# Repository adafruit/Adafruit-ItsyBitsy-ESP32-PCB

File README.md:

## Adafruit ItsyBitsy ESP32 8 MB Flash / 2 MB PSRAM PCB

<a href="http://www.adafruit.com/products/5889"><br/>
Click here to purchase one from the Adafruit shop</a>

PCB files for the Adafruit ItsyBitsy ESP32 8 MB Flash / 2 MB PSRAM: wFL Antenna and PCB Antenna. 

Format is EagleCAD schematic and board layout
* https://www.adafruit.com/product/5889
* https://www.adafruit.com/product/5890

### Description

What's smaller than a Feather but larger than a Trinket? It's an Adafruit ItsyBitsy ESP32, a powerful processor PCB with a plethora of pins! It features the ESP32 Pico module, an FCC-certified module that contains an ESP32 chip with dual-core 240MHz Tensilica processor, WiFi, and Bluetooth classic + BLE, configured with 8 MB of Flash memory, and 2 MB of PSRAM.

We've added some handy accessories like a USB to serial converter chip, power regulator, USB Micro B, buttons, NeoPixel, and Stemma QT I2C connector to outfit this super-hero chip for any task you want to throw it at. This is also an ultra low power ESP32 board with a deep sleep current consumption of 10uA!

At the core of the Itsy is the ESP32 (PICO ECO V3) chip, which is a single 2.4 GHz Wi-Fi and Bluetooth combo chip designed with TSMC’s 40 nm low-power technology. The ESP32 PICO in particular integrates all peripheral components seamlessly, including a crystal oscillator, flash, PSRAM, filter capacitors, and RF matching links in one single package. This makes it perfect for stuffing into a small space as the ItsyBitsy.

Please note, like other ESP32 modules, the ItsyBitsy ESP32 does not have native USB support - instead, there's a USB to serial converter chip. This means it cannot act like a USB keyboard or mouse, but it does have BLE and BT classic, so you could use it wirelessly.

Here are some of the updates you can look forward to when using ItsyBitsy ESP32:

* Same size, form-factor as the remaining ItsyBitsy mainboards - with a similar but not identical pinout (there are no pins at the end of the board like most other Itsy's due to the radio antenna being there)
* USB Micro B - To maintain compatibility with the rest of the ItsyBitsy's
* ESP32 V2 03 Dual Core 240MHz Xtensa processor - the ESP32 you know and love, with the latest engineering fixes. Massive user base and thousands of existing projects and libraries to use.
* WiFi, Bluetooth LE, and BT Classic for any IoT project usage
* 8 MB Flash & 2 MB PSRAM
* USB to Serial converter built-in with high-speed UART for debugging and uploading, auto-reset circuit works perfectly with any ESP32 uploading tool.
* Can be used with Arduino IDE, CircuitPython or MicroPython
* Built-in RGB NeoPixel LED with power control to reduce quiescent power in deep sleep
* Built-in Red LED on pin D13
* 5V level-shifted output on D5, perfect for driving NeoPixels or other devices that want 5V logic signal
* Battery input pads on the underside with diode protection for external battery packs up to 6V input
* 20 General Purpose "IO" pins:
	* 20 Pads expose pins from the ESP32:
	* 3 are analog input only (A3, A4, A5)
	* 1 is digital output only (5) with 5V level shifted up
	* 13 x 12-bit analog inputs (A0, A1, A2, A3, A4, A5, D12, D13, D14, SDA, SCL, D32, D33)
	* Dual 8-bit analog output DACs on A0/A1
	* PWM outputs on any pin
	* I2C port with STEMMA QT plug-n-play connector - a second I2C port can be defined on any other pins.
	* Hardware UART in addition to the USB-serial UART
	* Hardware SPI on the high speed SPI peripheral pins - a second SPI port can be defined on any other pins.
	* Hardware I2S on any pins
	* 8 x Capacitive Touch with no additional components required
* 3.3V regulator with 600mA peak output
* Light sleep at 4mA, deep sleep at ~10uA
* Reset switch for starting your project code over, for entering bootloader mode or for user reading
* User switch on pin 35
* Really small

Each order comes with one assembled and tested ItsyBitsy ESP32 with headers that can be soldered in for use with a breadboard.

### License

Adafruit invests time and resources providing this open source design, please support Adafruit and open-source hardware by purchasing products from [Adafruit](https://www.adafruit.com)!

Designed by Limor Fried/Ladyada for Adafruit Industries.

Creative Commons Attribution/Share-Alike, all text above must be included in any redistribution. 
See license.txt for additional details.

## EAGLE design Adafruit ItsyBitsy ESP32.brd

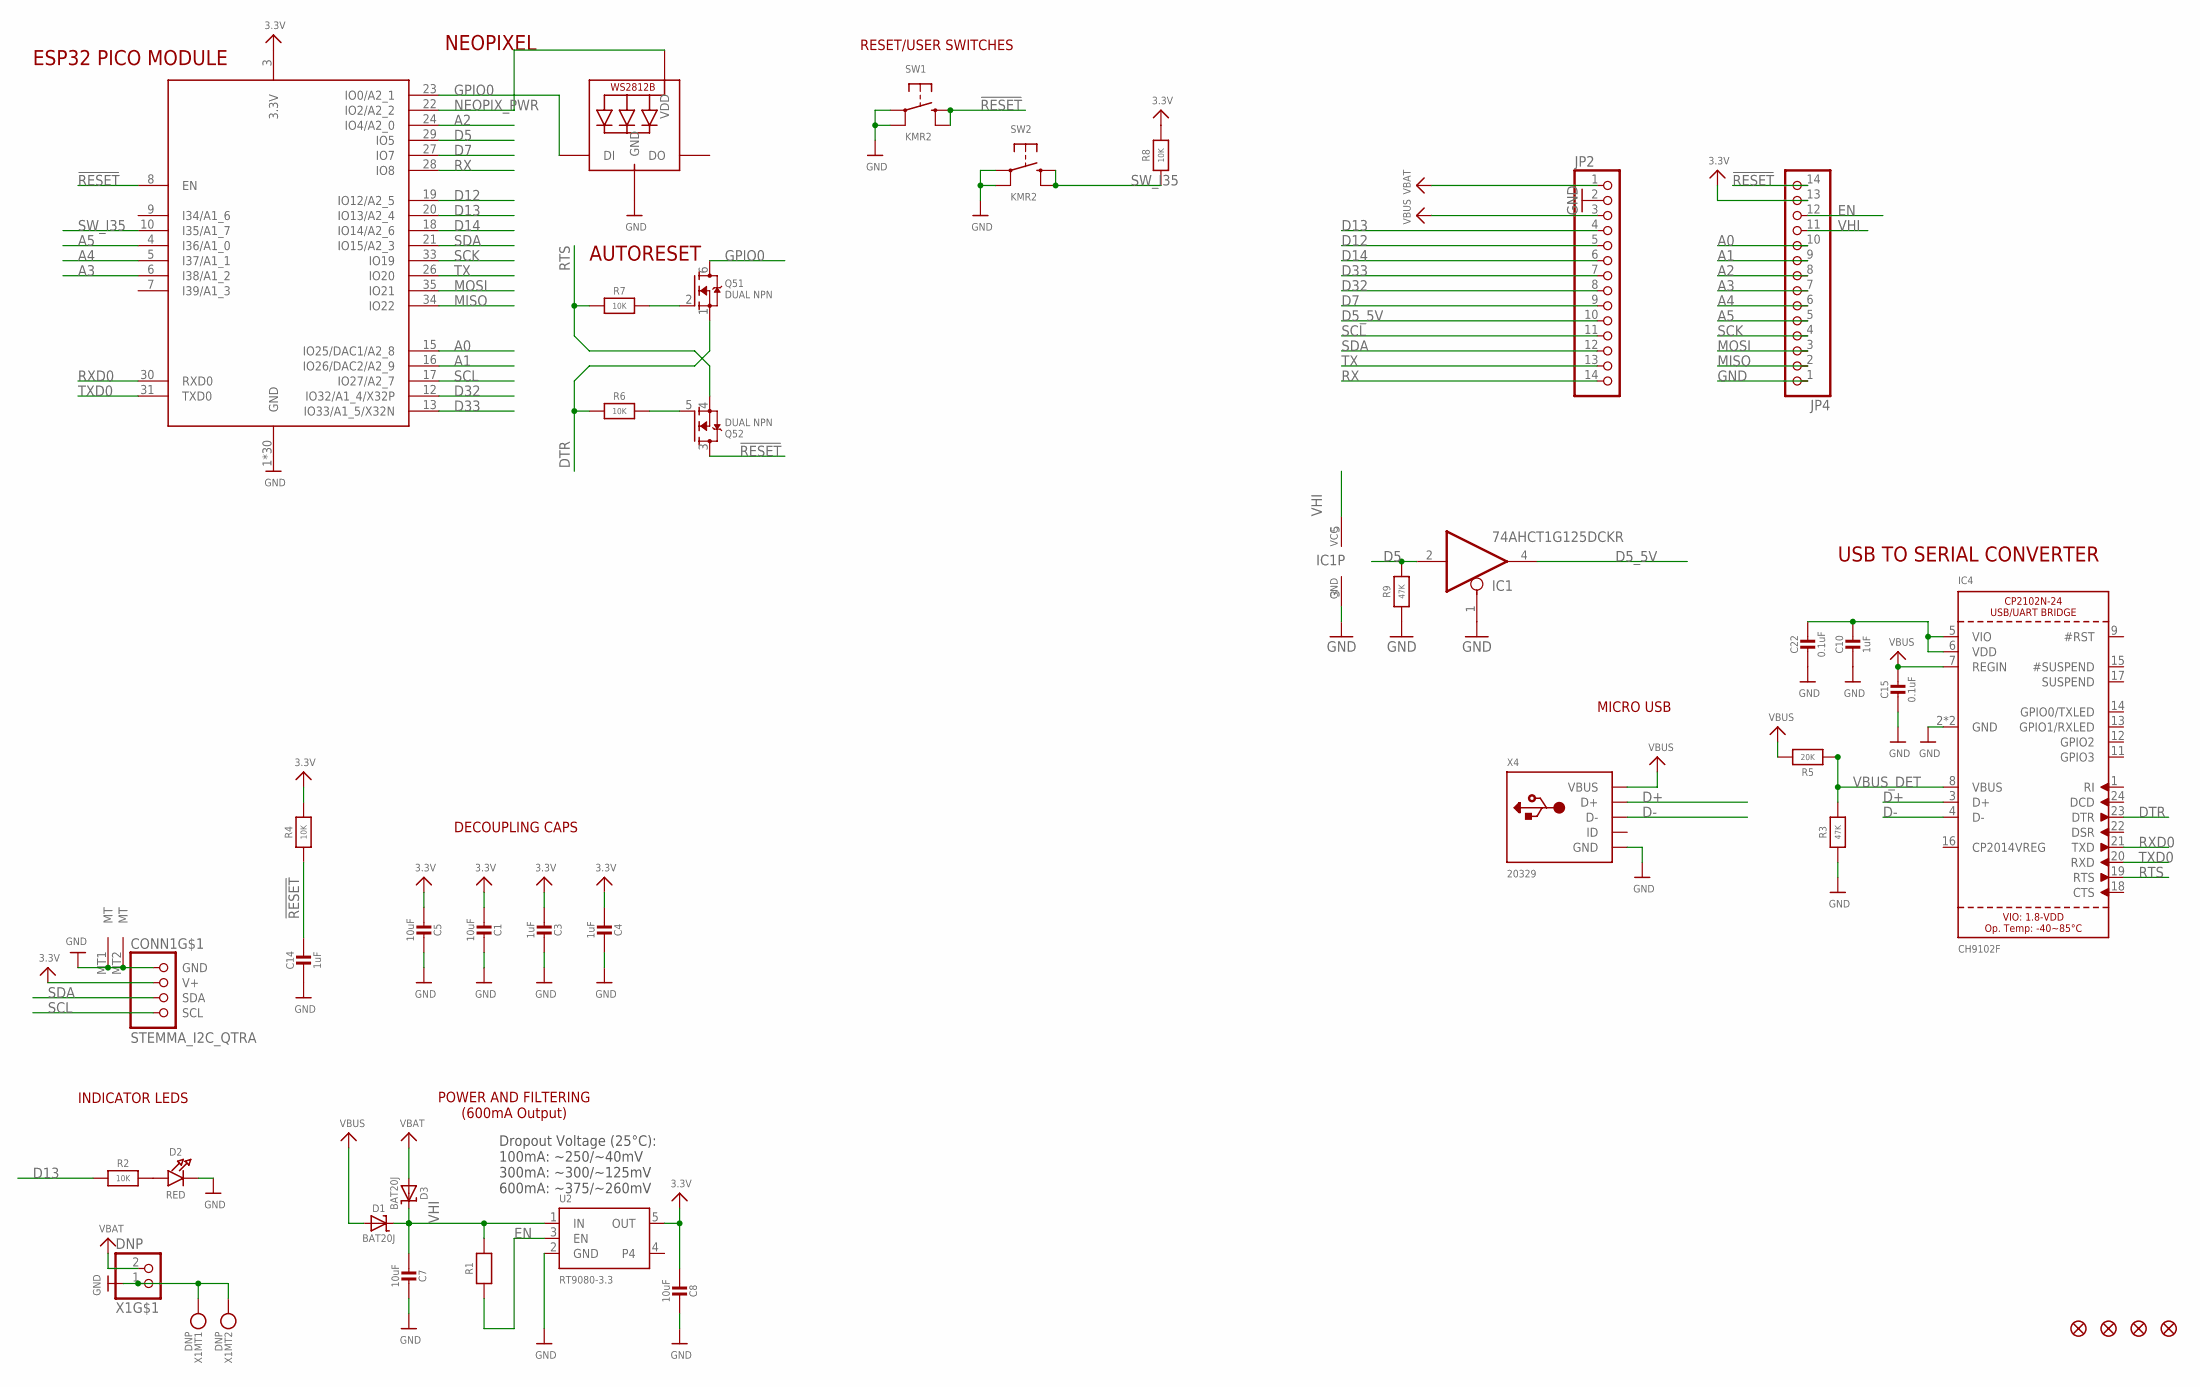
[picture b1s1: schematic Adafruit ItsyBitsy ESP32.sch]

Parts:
C1, C5, C7, C8: 10uF; 0805-NO
C3, C4, C10, C14: 1uF; 0603-NO
C15, C22: 0.1uF; 0603-NO
CONN1: STEMMA_I2C_QTRA; JST_SH4_RA
D1, D3: BAT20J; SOD-323
D2: RED; CHIPLED_0603_NOOUTLINE
FID1, FID2, FID3, FID4: FIDUCIAL_1MM
IC1: 74AHCT1G125DCKR; SC70-5
IC4: CH9102F; QFN24_4MM_SMSC
JP2, JP4: HEADER-1X14; 1X14_ROUND70
LED2: WS2812B_SK6805_1515; SK6805_1515
Q5: DUAL NPN; SOT363; JLC_ROTATION 0
R1, R2, R4, R6, R7, R8: 10K; 0603-NO
R3, R9: 47K; 0603-NO
R5: 20K; 0603-NO
SW1, SW2: KMR2; BTN_RKB2_4.6X2.8
U2: RT9080-3.3; SOT23-5; JLC_ROTATION 0
X1: DNP; JSTPH2_BATT
X3: ESP32-PICO-MINI-02MINI; ESP32-PICO-MINI
X4: 20329; 4UCONN_20329_SLIM

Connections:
3.3V: C1.2, C3.2, C4.2, C5.2, C8.2, CONN1.2 (V+), JP4.13, R4.2, R8.2, U2.5 (OUT), X3.3 (3.3V)
3.45V: C10.1, C22.1, IC4.5 (VIO), IC4.6 (VDD)
!RESET: C14.1, JP4.14, Q5.3 (D), R4.1, SW1.B (S), SW1.B' (S1), X3.8 (EN)
A0: JP4.10, X3.15 (IO25/DAC1/A2_8)
A1: JP4.9, X3.16 (IO26/DAC2/A2_9)
A2: JP4.8, X3.24 (IO4/A2_0)
A3: JP4.7, X3.6 (I38/A1_2)
A4: JP4.6, X3.5 (I37/A1_1)
A5: JP4.5, X3.4 (I36/A1_0)
D5: IC1.2 (I), R9.2, X3.29 (IO5)
D5_5V: IC1.4 (O), JP2.10
D7: JP2.9, X3.27 (IO7)
D12: JP2.5, X3.19 (IO12/A2_5)
D13: JP2.4, R2.1, X3.20 (IO13/A2_4)
D14: JP2.6, X3.18 (IO14/A2_6)
D32: JP2.8, X3.12 (IO32/A1_4/X32P)
D33: JP2.7, X3.13 (IO33/A1_5/X32N)
D+: IC4.3 (D+), X4.D+
D-: IC4.4 (D-), X4.D-
DTR: IC4.23 (DTR), Q5.1 (S), R6.1
EN: JP4.12, R1.1, U2.3 (EN)
GND: C1.1, C3.1, C4.1, C5.1, C7.1, C8.1, C10.2, C14.2, C15.2, C22.2, CONN1.1 (GND), CONN1.MT1 (MT), CONN1.MT2 (MT), D2.C, IC1.1 (OE), IC1.3 (GND), IC4.2 (GND), IC4.THERM (GND), JP2.2, JP4.1, LED2.4 (GND), R3.1, R9.1, SW1.A, SW1.A' (P1), SW2.A, SW2.A' (P1), U2.2 (GND), X1.1, X1.NC1, X1.NC2, X3.1 (GND), X3.2 (GND), X3.11 (GND), X3.14 (GND), X3.36 (GND), X3.37 (GND), X3.38 (GND), X3.39 (GND), X3.40 (GND), X3.41 (GND), X3.42 (GND), X3.43 (GND), X3.44 (GND), X3.45 (GND), X3.46 (GND), X3.47 (GND), X3.48 (GND), X3.49 (GND), X3.50 (GND), X3.51 (GND), X3.52 (GND), X3.53 (GND), X3.54 (GND), X3.55 (GND), X3.56 (GND), X3.57 (GND), X3.58 (GND), X3.59 (GND), X3.60 (GND), X3.61 (GND), X4.BASE@1 (GND), X4.BASE@2 (GND), X4.GND, X4.SPRT@1 (GND), X4.SPRT@2 (GND), X4.SPRT@3 (GND), X4.SPRT@4 (GND)
GPIO0: LED2.1 (DI), Q5.6 (D), X3.23 (IO0/A2_1)
MISO: JP4.2, X3.34 (IO22)
MOSI: JP4.3, X3.35 (IO21)
unnamed: D2.A, R2.2
unnamed: Q5.5 (G), R6.2
unnamed: Q5.2 (G), R7.2
NEOPIX_PWR: LED2.2 (VDD), X3.22 (IO2/A2_2)
RTS: IC4.19 (RTS), Q5.4 (S), R7.1
RX: JP2.14, X3.28 (IO8)
RXD0: IC4.21 (TXD), X3.30 (RXD0)
SCK: JP4.4, X3.33 (IO19)
SCL: CONN1.4 (SCL), JP2.11, X3.17 (IO27/A2_7)
SDA: CONN1.3 (SDA), JP2.12, X3.21 (IO15/A2_3)
SW_I35: R8.1, SW2.B (S), SW2.B' (S1), X3.10 (I35/A1_7)
TX: JP2.13, X3.26 (IO20)
TXD0: IC4.20 (RXD), X3.31 (TXD0)
VBAT: D3.A, JP2.1, X1.2
VBUS: C15.1, D1.A, IC4.7 (REGIN), JP2.3, R5.2, X4.VBUS
VBUS_DET: IC4.8 (VBUS), R3.2, R5.1
VHI: C7.2, D1.C, D3.C, IC1.5 (VCC), JP4.11, R1.2, U2.1 (IN)

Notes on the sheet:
POWER AND FILTERING (600mA Output)
Dropout Voltage (25°C): 100mA: ~250/~40mV 300mA: ~300/~125mV 600mA: ~375/~260mV
INDICATOR LEDS
RESET/USER SWITCHES
DECOUPLING CAPS
MICRO USB
ESP32 PICO MODULE
AUTORESET
NEOPIXEL
USB TO SERIAL CONVERTER

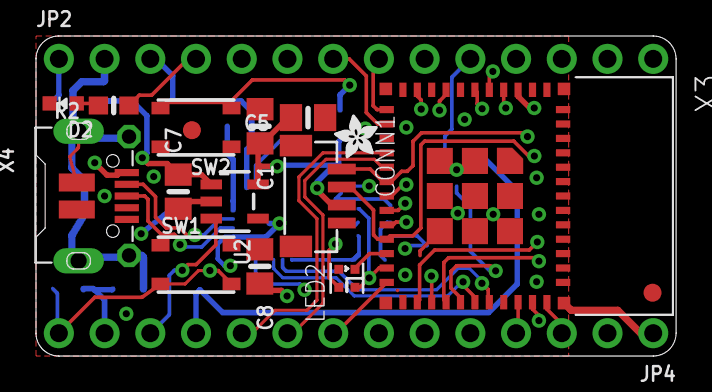
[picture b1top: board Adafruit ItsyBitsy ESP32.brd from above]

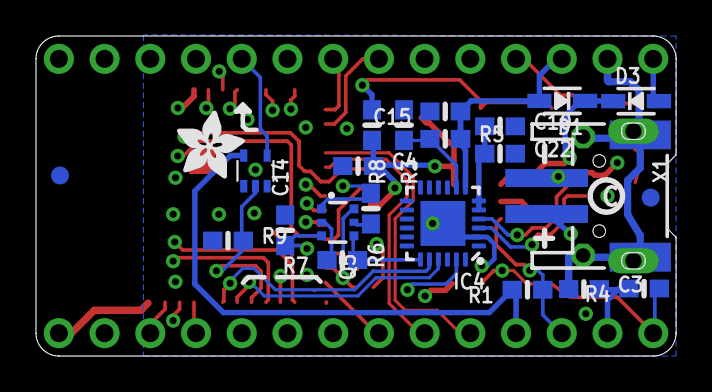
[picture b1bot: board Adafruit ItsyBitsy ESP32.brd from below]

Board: 4 copper layers, 35.6 x 17.8 mm, 87 parts (48 on the bottom side), 42 nets.

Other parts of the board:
E$1: ADAFRUIT_2.5MM
E$2: ADAFRUIT_3.5MM
PLABEL0: PLABEL0
PLABEL1: PLABEL1
PLABEL2: PLABEL2
PLABEL3: PLABEL3
PLABEL4: PLABEL4
PLABEL5: PLABEL5
PLABEL6: PLABEL6
PLABEL7: PLABEL7
PLABEL8: PLABEL8
PLABEL9: PLABEL9
PLABEL10: PLABEL10
PLABEL11: PLABEL11
PLABEL12: PLABEL12
PLABEL13: PLABEL13
PLABEL14: PLABEL14
PLABEL15: PLABEL15
PLABEL16: PLABEL16
PLABEL17: PLABEL17
PLABEL18: PLABEL18
PLABEL19: PLABEL19
PLABEL20: PLABEL20
PLABEL21: PLABEL21
PLABEL22: PLABEL22
PLABEL23: PLABEL23
PLABEL24: PLABEL24
PLABEL25: PLABEL25
PLABEL26: PLABEL26
PLABEL27: PLABEL27
PLABEL28: PLABEL28
PLABEL29: PLABEL29
PLABEL30: PLABEL30
PLABEL31: PLABEL31
PLABEL32: PLABEL32
PLABEL33: PLABEL33
PLABEL34: PLABEL34
PLABEL35: PLABEL35
PLABEL36: PLABEL36
PLABEL37: PLABEL37
PLABEL38: PLABEL38
PLABEL39: PLABEL39
PLABEL40: PLABEL40
PLABEL41: PLABEL41
PLABEL42: PLABEL42
PLABEL43: PLABEL43
PLABEL44: PLABEL44
U$16: PCBFEAT-REV-040

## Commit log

2024-02-21 cookiecutter
2024-02-21 wfl antenna link
2024-02-21 adding prettypins
2024-02-26 adding factory reset bin file

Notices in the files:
parts and their libraries:
microbuilder: This work is placed in the public domain, and may be freely used for commercial and non-commercial work with the following conditions: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
